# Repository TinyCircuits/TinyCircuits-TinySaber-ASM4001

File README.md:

# TinyCircuits-TinySaber-ASM4001
# ASM4001 Rev3

The design files are located under design_files/ for the TinyCircuits ASM4001 Rev 3 PCB. This is a touch-sensitive TinySaber made with RGB LEDs powered by Arduino software.

Format is in Cadsoft Eagle format - Eagle version 6.2 was used for the original design.

For more infomation on this, check out the product page at TinyCircuits.com: https://tinycircuits.com/collections/all/products/pocket-arcade

# License:

Design by TinyCircuits.
All design files are released under the Creative Commons Attribution Share-Alike 3.0 License, see the following link for details: http://creativecommons.org/licenses/by-sa/3.0

All text above must be included in any redistribution or derived design

This project uses designs and concepts developed as part of the Arduino project and the LilyPad project. The TinyCircuits design files themselves (schematics, PCB and libraries) are not directly derived from these works' design files and have been created new, however the concepts and basic architecture behind the TinyDuino and TinyLily products are derived and we thank the hard work of the organizations below for their contributions to open-source hardware:
  
Original Arduino Uno Design by Team Arduino

LilyPad Arduino Design by Leah Buechley and Sparkfun Electronics

Please support the open-source hardware community

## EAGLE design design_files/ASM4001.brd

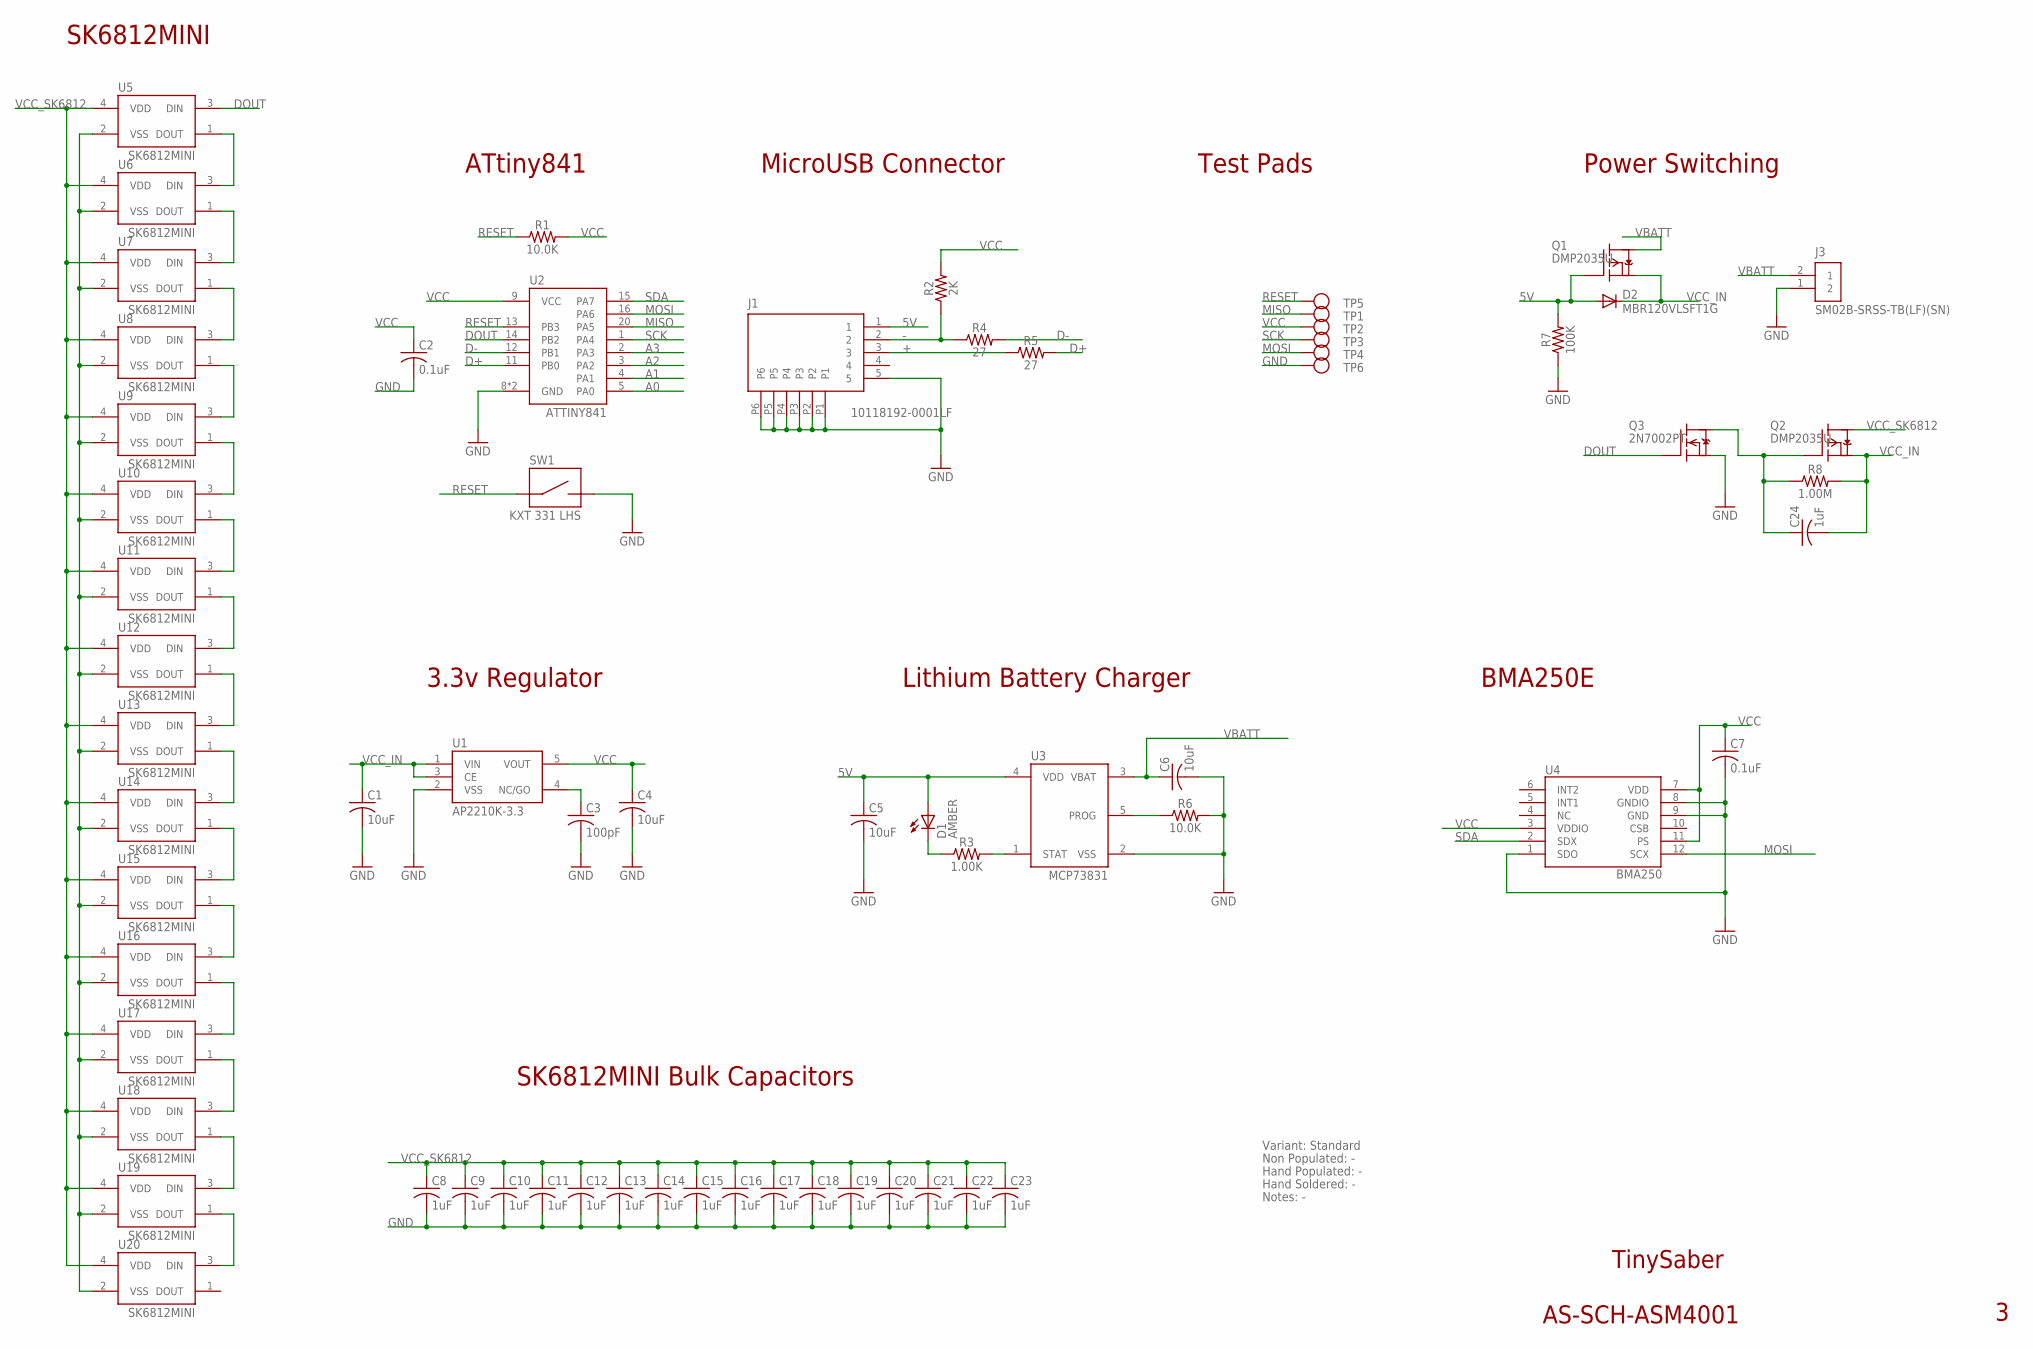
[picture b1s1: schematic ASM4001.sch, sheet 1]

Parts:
C1, C4, C5: 10uF; C0603; PARTNO AS-ITM-00002
C2, C7: 0.1uF; C0402
C3: 100pF; 0402; PARTNO AS-ITM-00148
C6: 10uF; C0603
C8, C9, C10, C11, C12, C13, C14, C15, C16, C17, C18, C19, C20, C21, C22, C23: 1uF; C0603; PARTNO AS-ITM-00410
C24: 1uF; C0402
D1: AMBER; 0402_LED
D2: MBR120VLSFT1G; SOD-123FL; PARTNO AS-ITM-00111
J1: 10118192-0001LF; MICRO_USB_ALT
J3: SM02B-SRSS-TB(LF)(SN); JST_SH_2X1
Q1: DMP2035U; SOT23
Q2: DMP2035U; SOT23A; PARTNO AS-ITM-00024
Q3: 2N7002PT; SOT-416
R1, R6: 10.0K; 0402
R2: 2K; 0402
R3: 1.00K; 0402
R4, R5: 27; 0402; PARTNO AS-ITM-00240
R7: 100K; 0402
R8: 1.00M; 0402; PARTNO AS-ITM-00005
SW1: KXT 331 LHS; KXT_LHS
TP1, TP2, TP3, TP4, TP5, TP6: TEST_POINT; TEST_POINT_1MM
U1: AP2210K-3.3; SOT-25; PARTNO AS-ITM-00344
U2: ATTINY841; VQFN-20
U3: MCP73831; SOT-23
U4: BMA250; 3-AXIS_ACCELEROMETER
U5, U6, U7, U8, U9, U10, U11, U12, U13, U14, U15, U16, U17, U18, U19, U20: SK6812MINI; PARTNO AS-ITM-00343

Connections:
5V: C5.1, D1.1 (A), D2.A, J1.1, Q1.B (G), R7.2, U3.4 (VDD)
+: J1.3, R5.1
-: J1.2, R2.1, R4.1
A0: U2.5 (PA0)
A1: U2.4 (PA1)
A2: U2.3 (PA2)
A3: U2.2 (PA3)
D+: R5.2, U2.11 (PB0)
D-: R4.2, U2.12 (PB1)
DOUT: Q3.1 (G), U2.14 (PB2), U5.3 (DIN)
GND: C1.2, C2.2, C3.2, C4.2, C5.2, C6.2, C7.2, C8.2, C9.2, C10.2, C11.2, C12.2, C13.2, C14.2, C15.2, C16.2, C17.2, C18.2, C19.2, C20.2, C21.2, C22.2, C23.2, J1.5, J1.P1, J1.P2, J1.P3, J1.P4, J1.P5, J1.P6, J3.1 (2), Q3.2 (S), R6.2, R7.1, SW1.2, TP6.P$1, U1.2 (VSS), U2.8 (GND), U2.PAD (GND), U3.2 (VSS), U4.1 (SDO), U4.8 (GNDIO), U4.9 (GND), U5.2 (VSS), U6.2 (VSS), U7.2 (VSS), U8.2 (VSS), U9.2 (VSS), U10.2 (VSS), U11.2 (VSS), U12.2 (VSS), U13.2 (VSS), U14.2 (VSS), U15.2 (VSS), U16.2 (VSS), U17.2 (VSS), U18.2 (VSS), U19.2 (VSS), U20.2 (VSS)
MISO: TP1.P$1, U2.20 (PA5)
MOSI: TP4.P$1, U2.16 (PA6), U4.12 (SCX)
unnamed: C3.1, U1.4 (NC/GO)
unnamed: U17.1 (DOUT), U18.3 (DIN)
unnamed: U18.1 (DOUT), U19.3 (DIN)
unnamed: U6.1 (DOUT), U7.3 (DIN)
unnamed: C24.1, Q2.B (G), Q3.3 (D), R8.1
unnamed: U19.1 (DOUT), U20.3 (DIN)
unnamed: R6.1, U3.5 (PROG)
unnamed: U5.1 (DOUT), U6.3 (DIN)
unnamed: U7.1 (DOUT), U8.3 (DIN)
unnamed: U8.1 (DOUT), U9.3 (DIN)
unnamed: R3.2, U3.1 (STAT)
unnamed: D1.2 (C), R3.1
unnamed: U9.1 (DOUT), U10.3 (DIN)
unnamed: U10.1 (DOUT), U11.3 (DIN)
unnamed: U11.1 (DOUT), U12.3 (DIN)
unnamed: U12.1 (DOUT), U13.3 (DIN)
unnamed: U13.1 (DOUT), U14.3 (DIN)
unnamed: U14.1 (DOUT), U15.3 (DIN)
unnamed: U15.1 (DOUT), U16.3 (DIN)
unnamed: U16.1 (DOUT), U17.3 (DIN)
RESET: R1.1, SW1.1, TP5.P$1, U2.13 (PB3)
SCK: TP3.P$1, U2.1 (PA4)
SDA: U2.15 (PA7), U4.2 (SDX)
VBATT: C6.1, J3.2 (1), Q1.C (D), U3.3 (VBAT)
VCC: C2.1, C4.1, C7.1, R1.2, R2.2, TP2.P$1, U1.5 (VOUT), U2.9 (VCC), U4.3 (VDDIO), U4.7 (VDD), U4.11 (PS)
VCC_IN: C1.1, C24.2, D2.C, Q1.E (S), Q2.E (S), R8.2, U1.1 (VIN), U1.3 (CE)
VCC_SK6812: C8.1, C9.1, C10.1, C11.1, C12.1, C13.1, C14.1, C15.1, C16.1, C17.1, C18.1, C19.1, C20.1, C21.1, C22.1, C23.1, Q2.C (D), U5.4 (VDD), U6.4 (VDD), U7.4 (VDD), U8.4 (VDD), U9.4 (VDD), U10.4 (VDD), U11.4 (VDD), U12.4 (VDD), U13.4 (VDD), U14.4 (VDD), U15.4 (VDD), U16.4 (VDD), U17.4 (VDD), U18.4 (VDD), U19.4 (VDD), U20.4 (VDD)

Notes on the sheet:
TinySaber
AS-SCH-ASM4001
Test Pads
MicroUSB Connector
ATtiny841
Power Switching
3.3v Regulator
Lithium Battery Charger
BMA250E
SK6812MINI
SK6812MINI Bulk Capacitors
Variant: Standard
Non Populated: -
Hand Populated: -
Hand Soldered: -
Notes: -

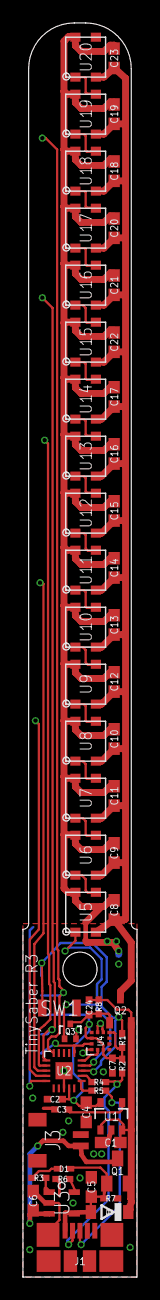
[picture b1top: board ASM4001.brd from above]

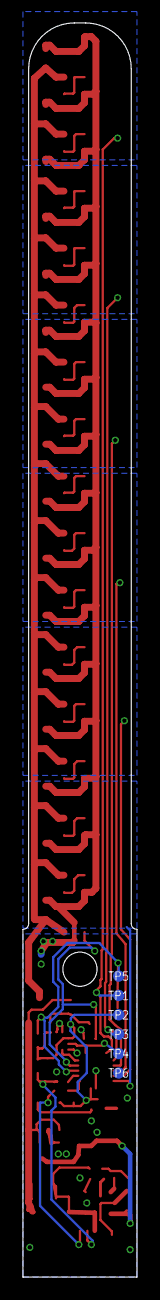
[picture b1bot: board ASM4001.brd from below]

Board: 2 copper layers, 10.0 x 110.0 mm, 67 parts (6 on the bottom side), 36 nets.

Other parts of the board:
U$1: DOCFIELD-TINYCIRCUITS-PCB

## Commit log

2019-10-17 design files
